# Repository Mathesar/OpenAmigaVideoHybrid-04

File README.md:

# OpenAmigaVideoHybrid-04
OpenAmigaVideoHybrid-04 is a fork from SukkoPera's [OpenAmigaVideoHybrid](https://github.com/SukkoPera/OpenAmigaVideoHybrid) which is an Open Hardware implementation of revision-03 of the Video Hybrid integrated circuit used in some Commodore Amiga computers (Commodore Part No. 390229-03).
This fork is a new revision (revision-04) optimized for automatic assembly at JLCPCB.

### Summary
The *Video Hybrid*, also known as *VIDIOT*, is a hybrid integrated circuit acting as a Digital-to-Analog Converter (DAC), which converts the digital 4-bit per color video signal of the Amiga into standard (analog) signals suitable to drive a monitor or TV.

It is used in Amiga models A500, A500+, A1000, A2000 and A3000. The Amiga 3000 actually uses two Hybrids: one for the 15kHz video output from Denise and one for the 31kHz video output from Amber. Two Hybrids are also used in the [GBA1000 A1000 Clone](https://www.amigawiki.org/doku.php?id=de:models:gb_a1000).

It is also used in some add-on cards, such as the [Commodore A2320 Deinterlacer](https://amiga.resource.cx/exp/a2320).

The Video Hybrid is a reliable component that usually "just works", but if it gets damaged there is no way of repairing it, the only option is to replace it.

### Architecture
The Video Hybrid has 5 sections, one for each of the red, green and blue colors, one for the synchronization signal and one for a composite monochrome signal.

The red, green and blue sections are identical: first, the digital signals are mixed together using the typical *binary-weighted resistors* DAC configuration. After that, the level of the resulting signal is amplified through an NPN transistor. At the output, the signal is terminated at 75 ohms, as is typical for video signals.

The composite signal is generated in a similar way. The only significant differences are that the weighting resistors have different values and that the amplifier has two stages (NPN + PNP), in order to achieve a higher gain.

The synchronization signal is digital by nature, thus it needs no conversion, only some amplification.

### Building
The board is optimized for production at JLCPCB using theit basic part library. All LCSC# partnumbers are included in the design. Check the releases for gerbers, BOM and schematics.

### License
OpenAmigaVideoHybrid is Open Hardware. If you make any modifications to the board, please contribute them back.

### Disclaimer
OpenAmigaVideoHybrid is provided to you ‘as is’ and without any express or implied warranties whatsoever with respect to its functionality, operability or use, including, without limitation, any implied warranties of merchantability, fitness for a particular purpose or infringement. We expressly disclaim any liability whatsoever for any direct, indirect, consequential, incidental or special damages, including, without limitation, lost revenues, lost profits, losses resulting from business interruption or loss of data, regardless of the form of action or legal theory under which the liability may be asserted, even if advised of the possibility or likelihood of such damages.

### Thanks
- [Sukkopera](https://github.com/SukkoPera) for making the OpenAmigaVideoHybrid.

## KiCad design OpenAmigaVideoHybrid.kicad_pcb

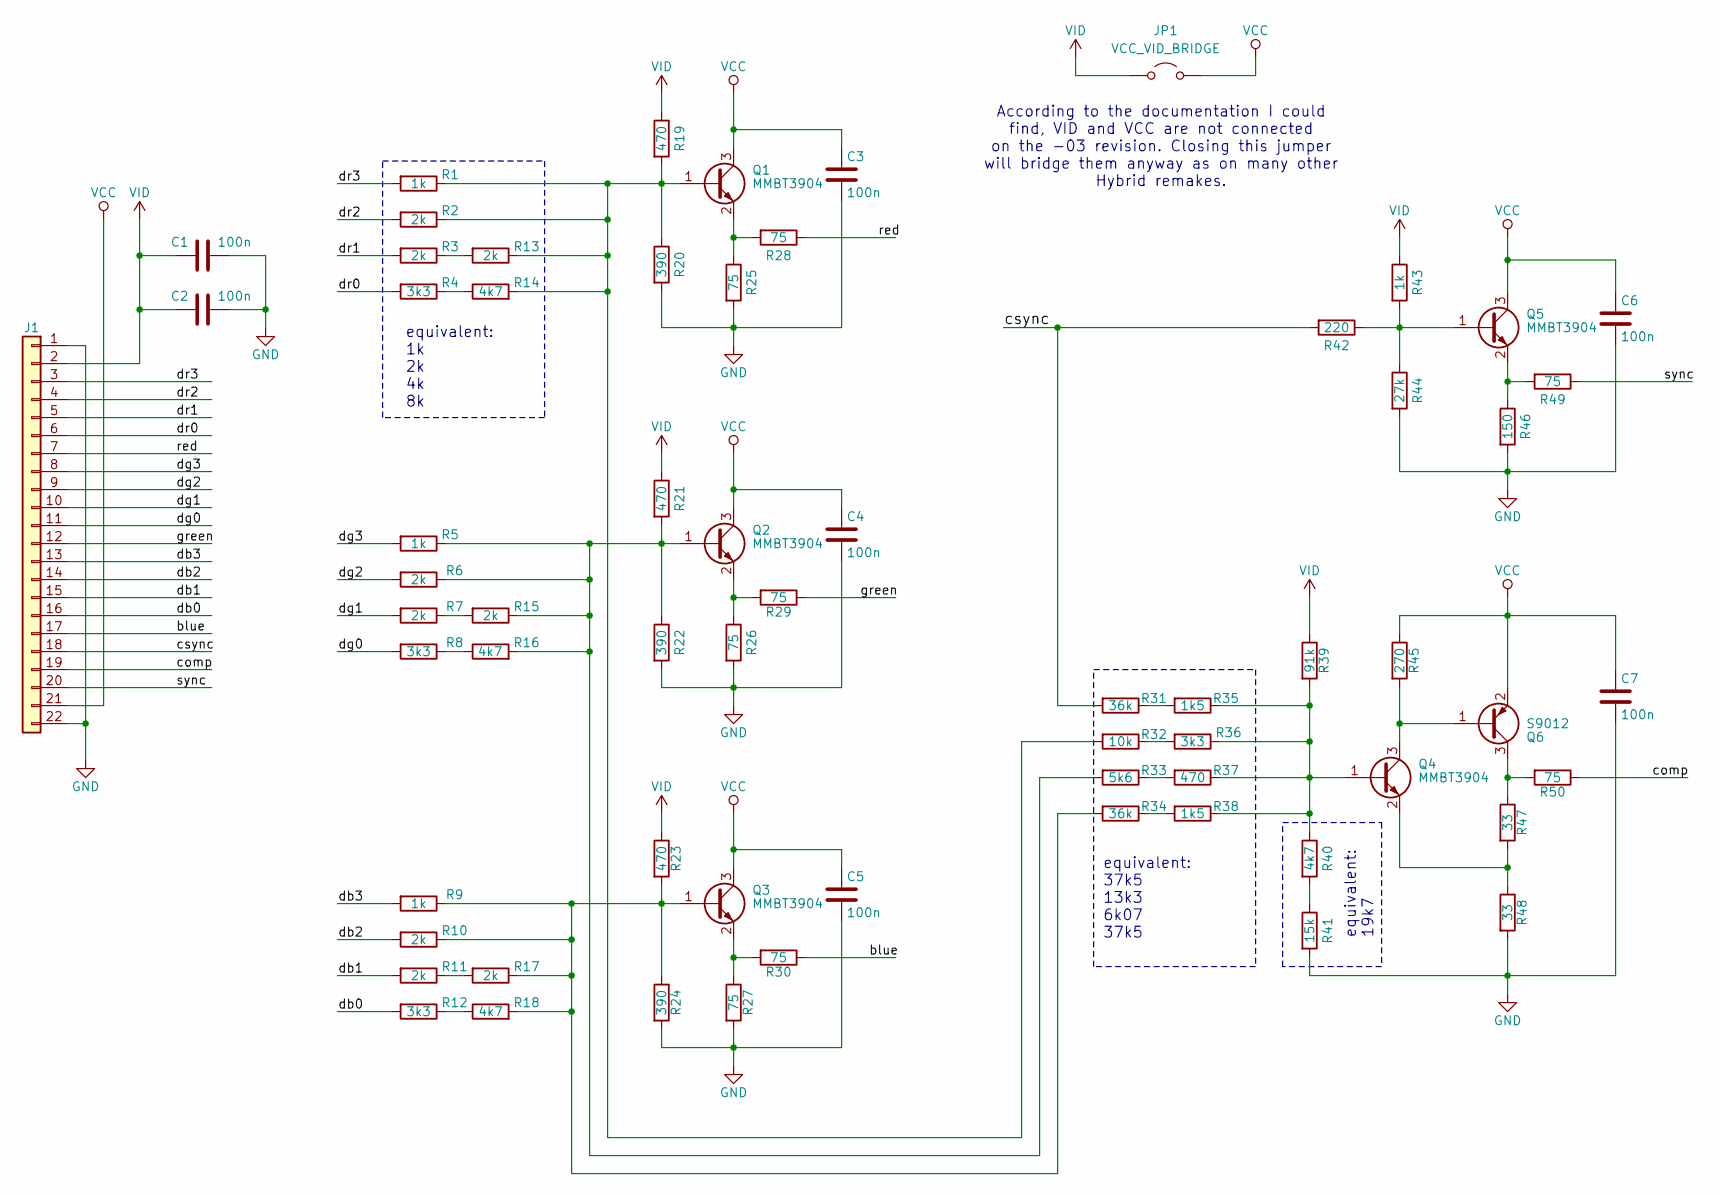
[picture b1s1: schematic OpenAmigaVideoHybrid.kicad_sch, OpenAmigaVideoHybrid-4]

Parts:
C1, C2, C3, C4, C5, C6, C7: 100n; C_0603_1608Metric; LCSC Part # C14663
J1: Conn_01x22; side_connector
JP1: VCC_VID_BRIDGE; SolderJumper-2_P1.3mm_Open_RoundedPad1.0x1.5mm
Q1, Q2, Q3, Q4, Q5: MMBT3904; SOT-23; LCSC Part # C20526
Q6: S9012; SOT-23; LCSC Part # C8543
R1, R5, R9, R43: 1k; R_0603_1608Metric; LCSC Part # C21190
R2, R3, R6, R7, R10, R11, R13, R15, R17: 2k; R_0603_1608Metric; LCSC Part # C22975
R4, R8, R12, R36: 3k3; R_0603_1608Metric; LCSC Part # C22978
R14, R16, R18, R40: 4k7; R_0603_1608Metric; LCSC Part # C23162
R19, R21, R23, R37: 470; R_0603_1608Metric; LCSC Part # C23179
R20, R22, R24: 390; R_0603_1608Metric; LCSC Part # C23151
R25, R26, R27, R28, R29, R30, R49, R50: 75; R_0603_1608Metric; LCSC Part # C4275
R31, R34: 36k; R_0603_1608Metric; LCSC Part # C23147
R32: 10k; R_0603_1608Metric; LCSC Part # C25804
R33: 5k6; R_0603_1608Metric; LCSC Part # C23189
R35, R38: 1k5; R_0603_1608Metric; LCSC Part # C22843
R39: 91k; R_0603_1608Metric; LCSC Part # C23265
R41: 15k; R_0603_1608Metric; LCSC Part # C22809
R42: 220; R_0603_1608Metric; LCSC Part # C22962
R44: 27k; R_0603_1608Metric; LCSC Part # C22967
R45: 270; R_0603_1608Metric; LCSC Part # C22966
R46: 150; R_0603_1608Metric; LCSC Part # C22808
R47, R48: 33; R_0603_1608Metric; LCSC Part # C23140

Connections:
/blue: J1.17, R30.1
/comp: J1.19, R50.1
/csync: J1.18, R31.2, R42.2
/db0: J1.16, R12.2
/db1: J1.15, R11.2
/db2: J1.14, R10.2
/db3: J1.13, R9.2
/dg0: J1.11, R8.2
/dg1: J1.10, R7.2
/dg2: J1.9, R6.2
/dg3: J1.8, R5.2
/dr0: J1.6, R4.2
/dr1: J1.5, R3.2
/dr2: J1.4, R2.2
/dr3: J1.3, R1.2
/green: J1.12, R29.1
/red: J1.7, R28.1
/sync: J1.20, R49.1
GND: C1.2, C2.2, C3.2, C4.2, C5.2, C6.2, C7.2, J1.1, J1.22, R20.2, R22.2, R24.2, R25.2, R26.2, R27.2, R41.2, R44.2, R46.2, R48.2
unnamed: Q1.1 (B), R1.1, R2.1, R13.1, R14.2, R19.2, R20.1, R32.2
unnamed: Q1.2 (E), R25.1, R28.2
unnamed: Q2.1 (B), R5.1, R6.1, R15.1, R16.2, R21.2, R22.1, R33.2
unnamed: Q2.2 (E), R26.1, R29.2
unnamed: Q3.1 (B), R9.1, R10.1, R17.1, R18.2, R23.2, R24.1, R34.2
unnamed: Q3.2 (E), R27.1, R30.2
unnamed: Q4.1 (B), R35.1, R36.1, R37.1, R38.1, R39.2, R40.1
unnamed: Q4.3 (C), Q6.1 (B), R45.2
unnamed: Q4.2 (E), R47.2, R48.1
unnamed: Q5.1 (B), R42.1, R43.2, R44.1
unnamed: Q5.2 (E), R46.1, R49.2
unnamed: Q6.3 (C), R47.1, R50.2
unnamed: R11.1, R17.2
unnamed: R12.1, R18.1
unnamed: R3.1, R13.2
unnamed: R4.1, R14.1
unnamed: R7.1, R15.2
unnamed: R8.1, R16.1
unnamed: R31.1, R35.2
unnamed: R32.1, R36.2
unnamed: R33.1, R37.2
unnamed: R34.1, R38.2
unnamed: R40.2, R41.1
VCC: C3.1, C4.1, C5.1, C6.1, C7.1, J1.21, JP1.2 (B), Q1.3 (C), Q2.3 (C), Q3.3 (C), Q5.3 (C), Q6.2 (E), R45.1
VID: C1.1, C2.1, J1.2, JP1.1 (A), R19.1, R21.1, R23.1, R39.1, R43.1

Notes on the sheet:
equivalent: 37k5 13k3 6k07 37k5
equivalent: 19k7
equivalent: 1k 2k 4k 8k
According to the documentation I could find, VID and VCC are not connected on the -03 revision. Closing this jumper will bridge them anyway as on many other Hybrid remakes.

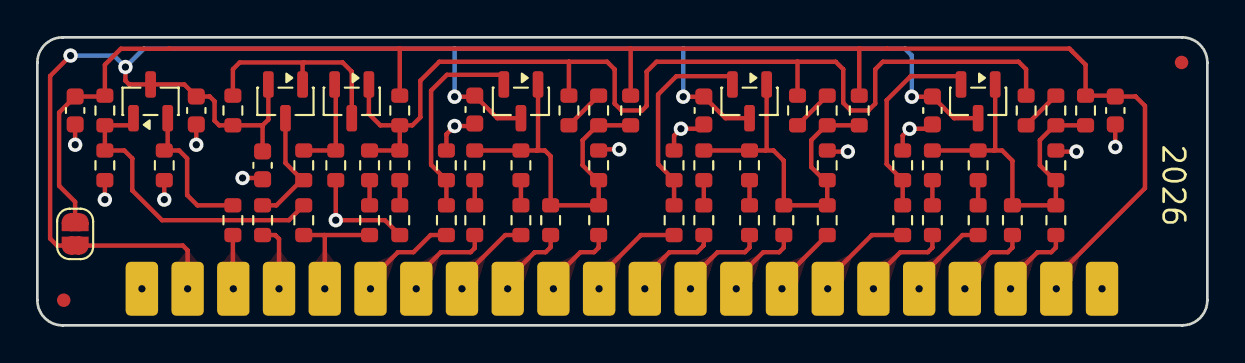
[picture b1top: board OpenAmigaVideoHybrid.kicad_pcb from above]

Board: 2 copper layers, 65.0 x 16.0 mm, 68 parts (1 on the bottom side), 44 nets.

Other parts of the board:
REF1, REF2: Fiducial_0.75mm_Mask1.5mm
REF3: OSHW-Symbol_6.7x6mm_SilkScreen

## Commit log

2026-02-13 Revise support and gratitude sections in README
2026-04-24 work in progress
2026-04-25 work done
2026-04-25 routing done
    DRC pass
    added fiducials and silkscreen
2026-04-25 designators renumbered
2026-04-25 updated BOM for assembly by JLCPCB
